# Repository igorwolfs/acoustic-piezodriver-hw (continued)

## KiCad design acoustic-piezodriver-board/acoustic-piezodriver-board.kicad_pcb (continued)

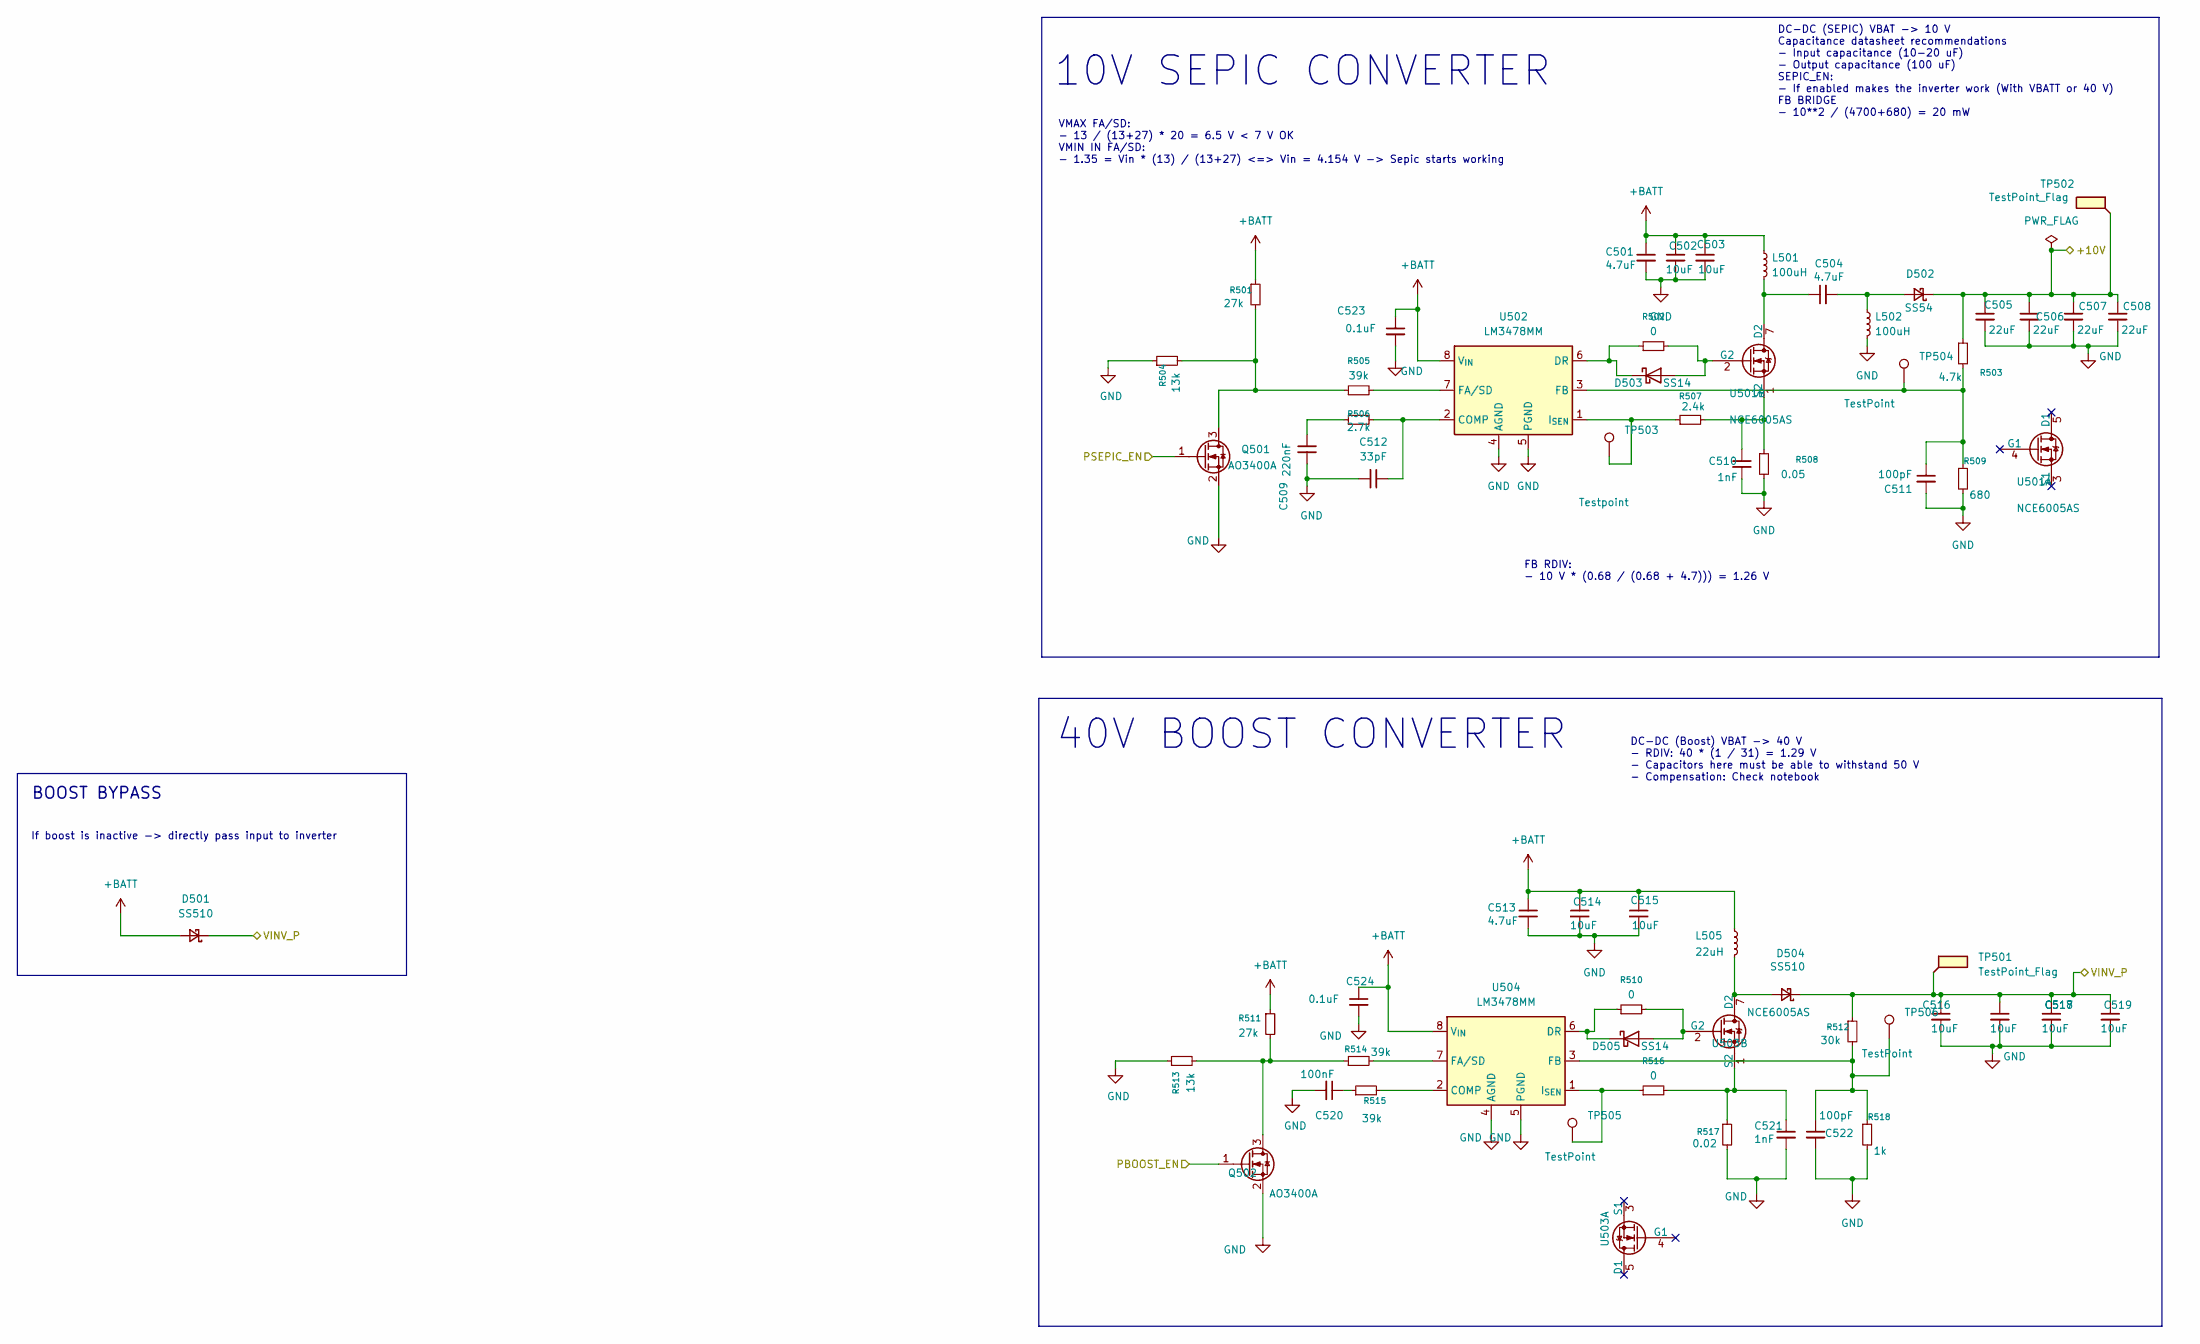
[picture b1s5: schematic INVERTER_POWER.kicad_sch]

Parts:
C501, C504, C513: 4.7uF; C_1206_3216Metric; Manufacturing Part Numb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 1206B475K500NT; LCSC Part Number C29823
C502, C503, C514, C515, C516, C517, C518, C519: 10uF; C_0805_2012Metric; Manufacturing Part Numb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 GRM21BR61H106KE43L; LCSC Part Number C440198
C505, C506, C507, C508: 22uF; C_0805_2012Metric; Manufacturing Part Numb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 CL21A226MAQNNNE; LCSC Part Number C45783
C509: 220nF; C_0805_2012Metric; Manufacturing Part Numb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 CL21B224KBFNNNE; LCSC Part Number C5378
C510, C521: 1nF; C_0402_1005Metric; Manufacturing Part Numb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 0402B102K500NT; LCSC Part Number C1523
C511, C522: 100pF; C_0402_1005Metric; Manufacturing Part Numb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 0402CG101J500NT; LCSC Part Number C1546
C512: 33pF; C_0603_1608Metric; Manufacturing Part Numb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 CL10C330JB8NNNC; LCSC Part Number C1663
C520: 100nF; C_0603_1608Metric; Manufacturing Part Numb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 CC0603KRX7R9BB104; LCSC Part Number C14663
C523, C524: 0.1uF; C_0402_1005Metric; Manufacturing Part Numb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 CL05B104KB54PNC; LCSC Part Number C307331
D501, D504: SS510; D_SMA; Manufacturing Part Numb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 SS510; LCSC Part Number C65010
D502: SS54; D_SMA; Manufacturing Part Numb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 SS54; LCSC Part Number C22452
D503, D505: SS14; D_SMA; Manufacturing Part Numb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 SS14; LCSC Part Number C2480
L501, L502: 100uH; PSPMAA1050H-101M-ANP; Manufacturing Part Numb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 PSPMAA1050H-101M-ANP; LCSC Part Number C5273830
L505: 22uH; PA4343.223NLT; Manufacturing Part Numb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 PA4343.223NLT; LCSC Part Number C2453841
Q501, Q502: AO3400A; SOT-23; Manufacturing Part Numb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 AO3400A; LCSC Part Number C20917
R501, R511: 27k; R_0603_1608Metric; Manufacturing Part Numb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 0603WAF2702T5E; LCSC Part Number C22967
R502, R510, R516: 0; R_0603_1608Metric_Pad0.98x0.95mm_HandSolder; Manufacturing Part Numb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 0603WAJ0000T5E; LCSC Part Number C15402
R503: 4.7k; R_0603_1608Metric; Manufacturing Part Numb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 0603WAF4701T5E; LCSC Part Number C23162
R504, R513: 13k; R_0603_1608Metric; Manufacturing Part Numb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 0603WAF1302T5E; LCSC Part Number C22797
R505, R514, R515: 39k; R_0603_1608Metric; Manufacturing Part Numb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 0603WAF3902T5E; LCSC Part Number C23153
R506: 2.7k; R_0603_1608Metric; Manufacturing Part Numb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 0603WAF2701T5E; LCSC Part Number C13167
R507: 2.4k; R_0805_2012Metric_Pad1.20x1.40mm_HandSolder; Manufacturing Part Numb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 0805W8F2401T5E; LCSC Part Number C17526
R508: 0.05; R_1206_3216Metric_Pad1.30x1.75mm_HandSolder; Manufacturing Part Numb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 1206W3F500MT5E; LCSC Part Number C127691
R509: 680; R_0603_1608Metric; Manufacturing Part Numb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 0603WAF6800T5E; LCSC Part Number C23228
R512: 30k; R_0603_1608Metric; Manufacturing Part Numb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 0603WAF3002T5E; LCSC Part Number C22984
R517: 0.02; R_1206_3216Metric_Pad1.30x1.75mm_HandSolder; Manufacturing Part Numb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 1206W3F200MT5E; LCSC Part Number C2765435
R518: 1k; R_0603_1608Metric; Manufacturing Part Numb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 0603WAF1001T5E; LCSC Part Number C21190
TP501, TP502: TestPoint_Flag; TestPoint_THTPad_D4.0mm_Drill2.0mm
TP503: Testpoint; TestPoint_Pad_D1.0mm
TP504, TP505, TP506: TestPoint; TestPoint_Pad_D1.0mm
U501, U503: NCE6005AS; SOIC-8_3.9x4.9mm_P1.27mm; Manufacturing Part Numb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 NCE6005AS; LCSC Part Number C126151
U502, U504: LM3478MM; VSSOP-8_3x3mm_P0.65mm; Manufacturing Part Numb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 LM3478MMX/NOPB; LCSC Part Number C404045

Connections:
+BATT: C501.1, C502.1, C503.1, C513.1, C514.1, C515.1, C523.1, C524.1, D501.2 (A), L501.1, L505.1, R501.1, R511.1, U502.8 (V_{IN}), U504.8 (V_{IN}); also elsewhere on the board
/INVERTER/+10V: C505.1, C506.1, C507.1, C508.1, D502.1 (K), R503.1, TP502.1; also elsewhere on the board
/INVERTER/PBOOST_EN: Q502.1 (G); also elsewhere on the board
/INVERTER/PSEPIC_EN: Q501.1 (G); also elsewhere on the board
/INVERTER/VINV_P: C516.1, C517.1, C518.1, C519.1, D501.1 (K), D504.1 (K), R512.1, TP501.1; also elsewhere on the board
GND: C501.2, C502.2, C503.2, C505.2, C506.2, C507.2, C508.2, C509.2, C510.2, C511.2, C512.2, C513.2, C514.2, C515.2, C516.2, C517.2, C518.2, C519.2, C520.2, C521.2, C522.2, C523.2, C524.2, L502.2, Q501.2 (S), Q502.2 (S), R504.1, R508.2, R509.2, R513.1, R517.2, R518.2, U502.4 (AGND), U502.5 (PGND), U504.4 (AGND), U504.5 (PGND); also elsewhere on the board
unnamed: C504.1, L501.2, U501.7 (D2), U501.8 (D2)
unnamed: C509.1, R506.1
unnamed: C520.1, R515.1
unnamed: C504.2, D502.2 (A), L502.1
unnamed: D503.2 (A), R502.2, U501.2 (G2)
unnamed: D503.1 (K), R502.1, U502.6 (DR)
unnamed: D504.2 (A), L505.2, U503.7 (D2), U503.8 (D2)
unnamed: D505.2 (A), R510.2, U503.2 (G2)
unnamed: D505.1 (K), R510.1, U504.6 (DR)
unnamed: Q501.3 (D), R501.2, R504.2, R505.1
unnamed: Q502.3 (D), R511.2, R513.2, R514.1
unnamed: C510.1, R507.2, R508.1, U501.1 (S2)
unnamed: C512.1, R506.2, U502.2 (COMP)
unnamed: R505.2, U502.7 (FA/SD)
unnamed: C511.1, R503.2, R509.1, TP504.1, U502.3 (FB)
unnamed: R507.1, TP503.1, U502.1 (I_{SEN})
unnamed: C521.1, R516.2, R517.1, U503.1 (S2)
unnamed: R515.2, U504.2 (COMP)
unnamed: R514.2, U504.7 (FA/SD)
unnamed: C522.1, R512.2, R518.1, TP506.1, U504.3 (FB)
unnamed: R516.1, TP505.1, U504.1 (I_{SEN})

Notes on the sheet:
DC-DC (Boost) VBAT -> 40 V - RDIV: 40 * (1 / 31) = 1.29 V - Capacitors here must be able to withstand 50 V - Compensation: Check notebook
DC-DC (SEPIC) VBAT -> 10 V Capacitance datasheet recommendations - Input capacitance (10-20 uF) - Output capacitance (100 uF) SEPIC_EN: - If enabled makes the inverter work (With VBATT or 40 V) FB BRIDGE - 10**2 / (4700+680) = 20 mW
10V SEPIC CONVERTER
FB RDIV: - 10 V * (0.68 / (0.68 + 4.7))) = 1.26 V
40V BOOST CONVERTER
VMAX FA/SD: - 13 / (13+27) * 20 = 6.5 V < 7 V OK VMIN IN FA/SD: - 1.35 = Vin * (13) / (13+27) <=> Vin = 4.154 V -> Sepic starts working
If boost is inactive -> directly pass input to inverter
BOOST BYPASS

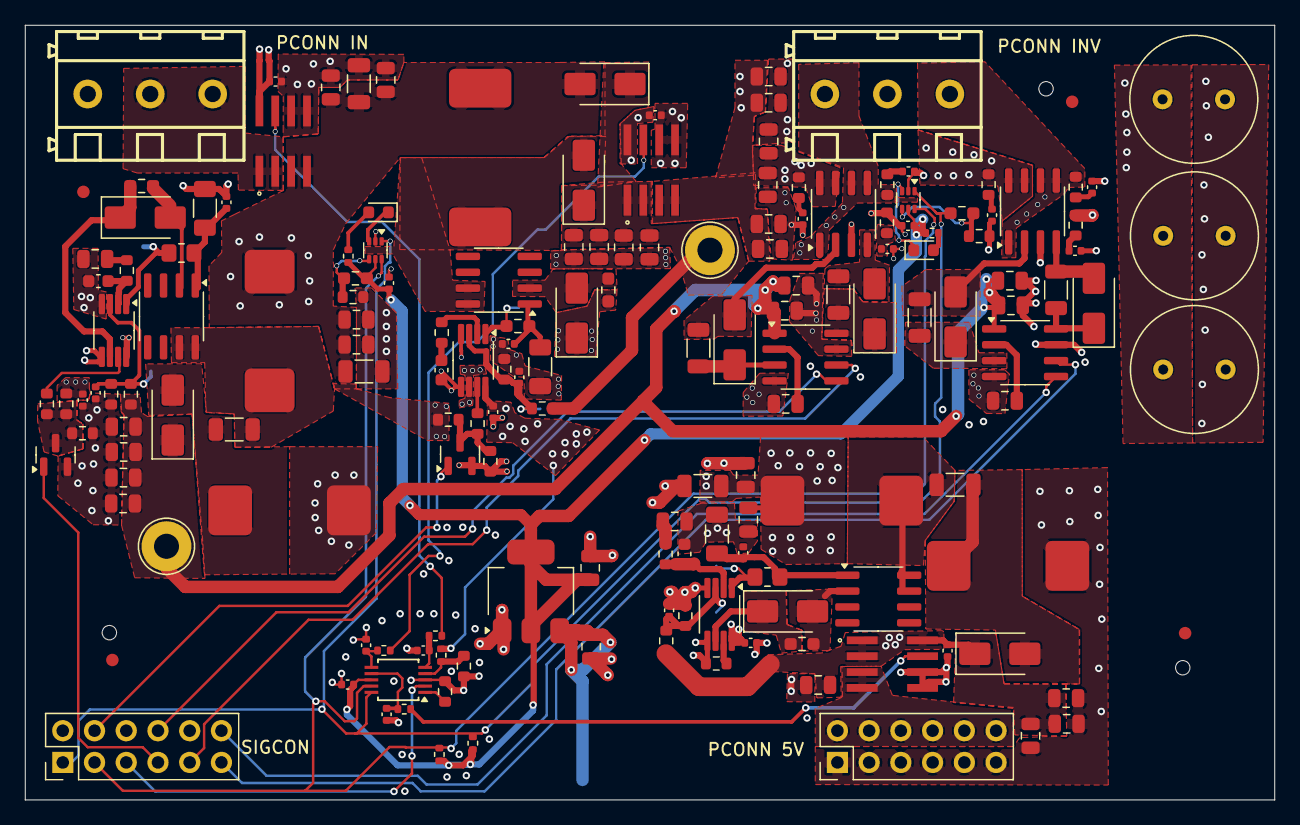
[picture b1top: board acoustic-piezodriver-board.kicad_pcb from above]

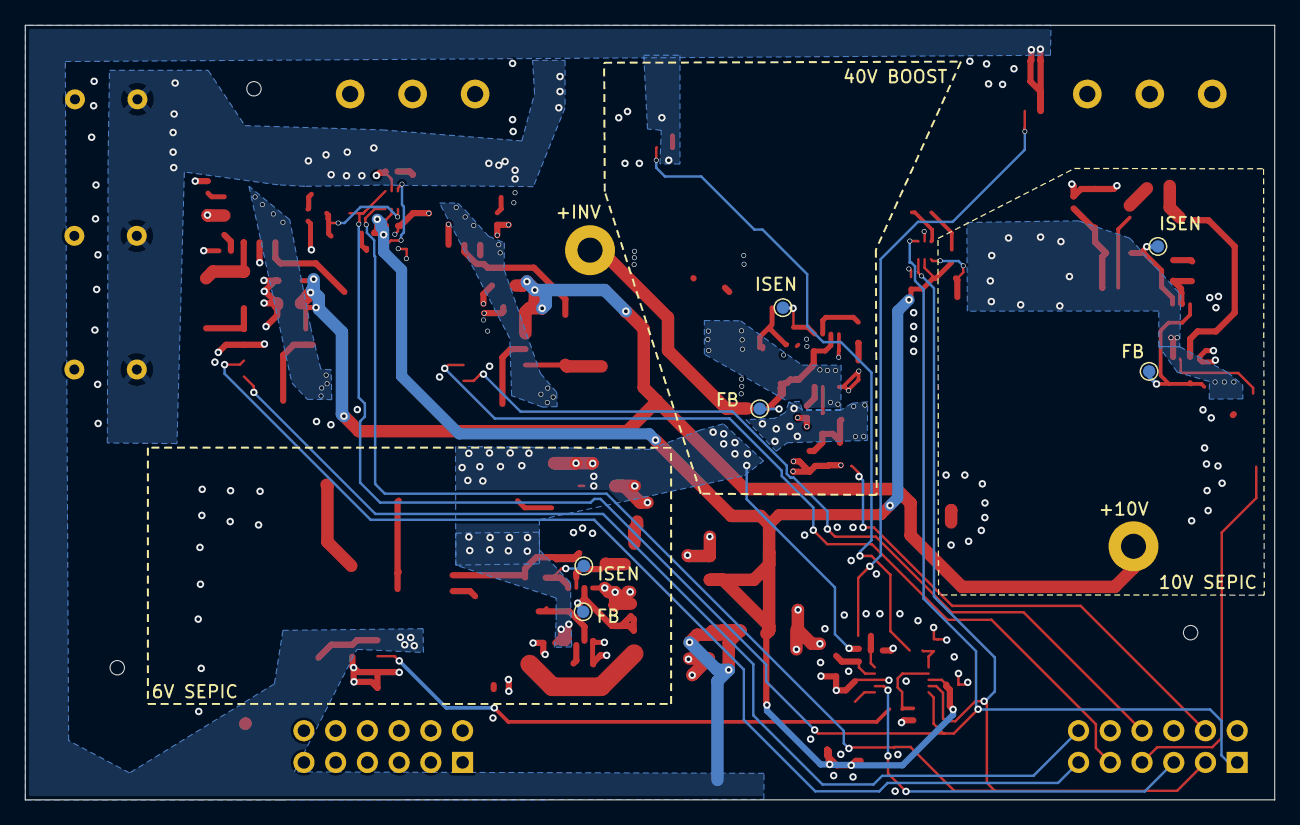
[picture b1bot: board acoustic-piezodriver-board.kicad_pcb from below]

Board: 4 copper layers, 100.0 x 62.0 mm, 174 parts (6 on the bottom side), 81 nets.

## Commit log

2025-07-28 [acoustic-processing-board] Added board as submodule
2025-07-28 stripped down repo to piezodriver board only
2025-07-29 [schematic] added adc for temperature measurement, current sense resistors, [layout] component placement, connector placement
2025-07-29 [piezodriver] Added resistive divider (next) come up with a solution for current sensing (galvanic isolation?)
2025-07-30 found hal-sensor, replaced with different one for lower voltage signal source impedance, reorganised schematic
2025-07-30 added new notes + schematic component hal sensors
2025-07-31 finished schematic, routing
2025-07-31 replaced dual 10uH inductors with single 22uH higher VDC resistant one, started laying out 40 V boost
2025-07-31 placed inverter and 40 V boost (next) place 10 V SEPIC driver
2025-07-31 rough layout completed, reduce board size and place components accordingly
2025-08-01 completed positioning (next) routing
2025-08-02 Did partial layout of inverter + 40 V boost + 10 V buck (next) Finish inverter, reorder and route SEPIC, check I2C bus capacitance limit
2025-08-04 main routing completed, finish 3V3 + I2C bus
2025-08-05 completed 3V3 routing
2025-08-06 Fixed ERC, DRC errors, finished routing (next) perform footprint checks
2025-08-10 changed footprints, changed stackup from L3:PWR-> L3:GND and routed +BATT on 4th layer
2025-08-10 [production checks] checked caps, [todo] Think about replacing 220 nF filtering caps in DC-DC to 0402 package (next) check rest of footprints
2025-08-11 changed ss520 footprints
2025-08-12 checked components until mosfets
2025-08-12 completed footprint check (next) reroute pbootstrap circuit on top layer only, fix errors after footprint change
2025-08-13 Modified feedback path for low-impedance signals tobe closer to FB pin
2025-08-15 fixed erc and drc errors completely, added 3d models for connectors, finished DFM (next) create gerbers, check
2025-08-16 added testpoints on fb and isense pins (next) double-check schematic and order
2025-08-17 added gerbers
2025-08-23 added lower side box for PCB
2025-08-25 added case changes
2025-09-04 Build box bottom (next) build box lid
2025-09-05 completed design (next) trying to 3D print M3-M4 thread
2025-09-07 minor change
2025-09-07 added driver-board-testcode
2025-09-18 attempting to figure out origin of short
2025-09-18 piezodriver-board-testcode/
